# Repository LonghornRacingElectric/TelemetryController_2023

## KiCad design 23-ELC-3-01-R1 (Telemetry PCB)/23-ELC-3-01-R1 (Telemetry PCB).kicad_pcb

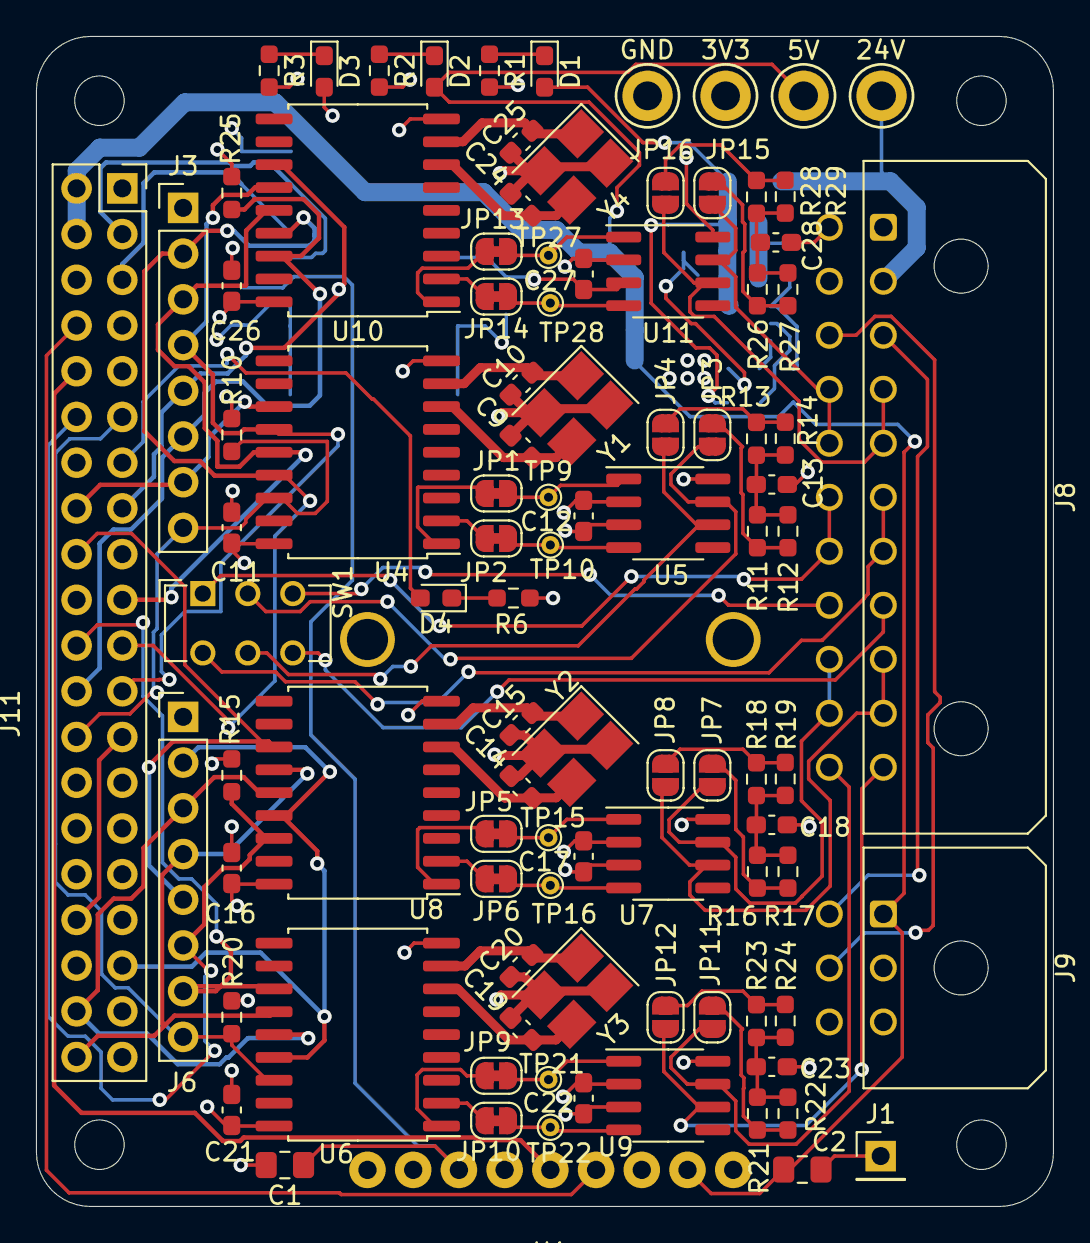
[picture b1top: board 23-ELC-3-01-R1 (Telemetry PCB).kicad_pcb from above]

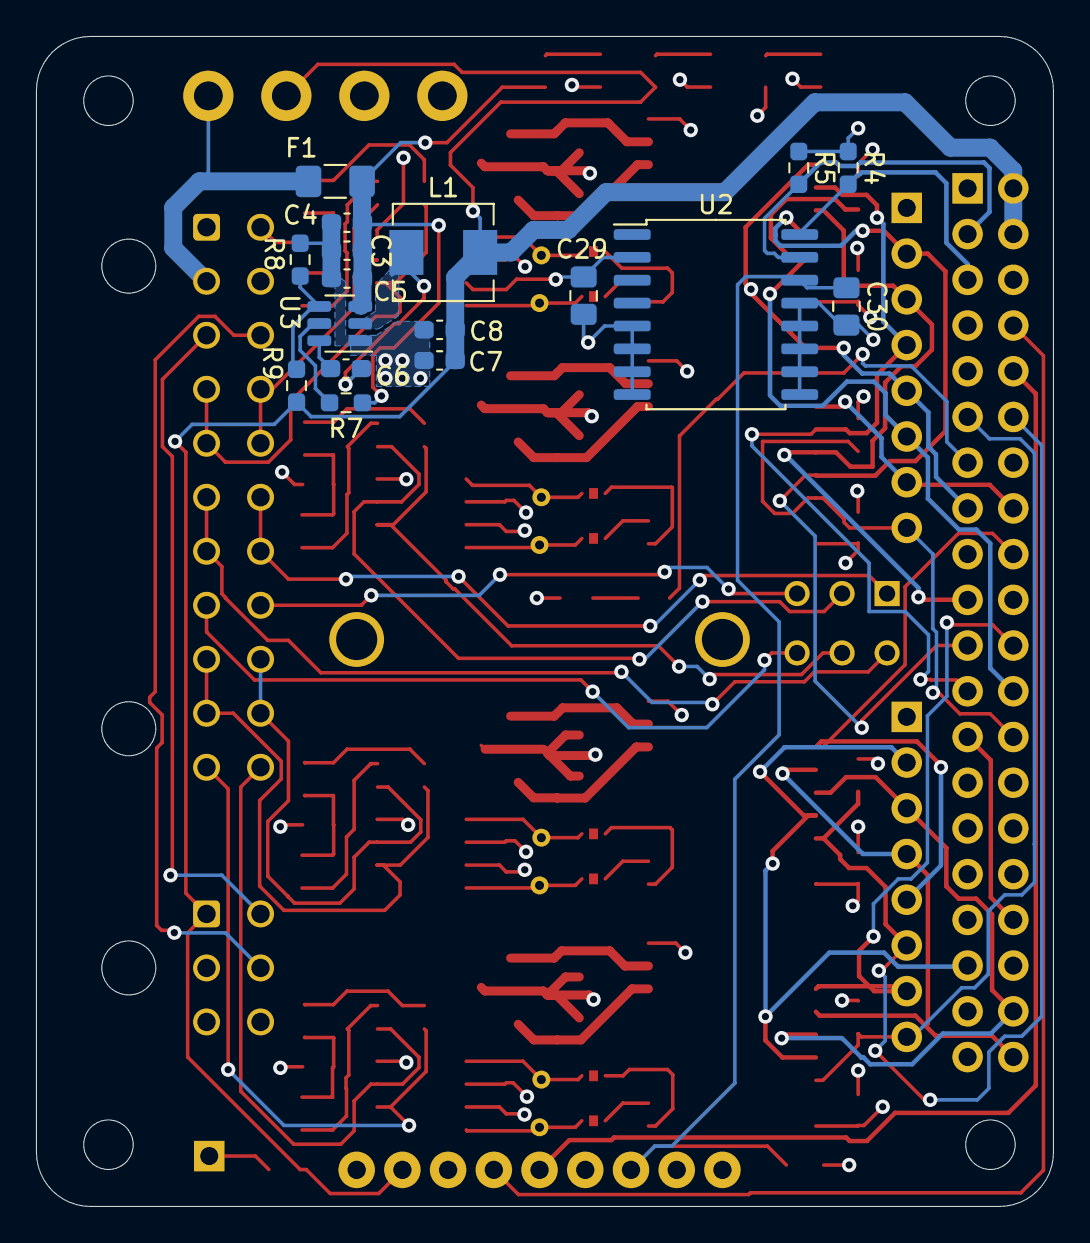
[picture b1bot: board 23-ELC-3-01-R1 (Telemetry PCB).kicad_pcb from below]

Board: 4 copper layers, 56.5 x 65.0 mm, 115 parts (17 on the bottom side), 83 nets.

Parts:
C1, C29, C30: 1uF; C_0805_2012Metric_Pad1.18x1.45mm_HandSolder
C2: 10uF; C_0805_2012Metric_Pad1.18x1.45mm_HandSolder
C3, C4: 10uF; C_0603_1608Metric_Pad1.08x0.95mm_HandSolder
C5, C6: 100nF; C_0603_1608Metric_Pad1.08x0.95mm_HandSolder
C7, C8: 22uF; C_0603_1608Metric_Pad1.08x0.95mm_HandSolder
C9, C10, C14, C15, C19, C20, C24, C25: 22pf; C_0603_1608Metric_Pad1.08x0.95mm_HandSolder
C11, C12, C16, C17, C21, C22, C26, C27: 0.1uf; C_0603_1608Metric_Pad1.08x0.95mm_HandSolder
C13, C18, C23, C28: 4.7nF; C_0603_1608Metric_Pad1.08x0.95mm_HandSolder
D1, D2, D3, D4: LED; LED_0603_1608Metric_Pad1.05x0.95mm_HandSolder
F1: 1A; Fuse_1206_3216Metric_Pad1.42x1.75mm_HandSolder
J1: Conn_01x01; PinHeader_1x01_P2.54mm_Vertical
J3, J6: Conn_01x08; PinHeader_1x08_P2.54mm_Vertical
J8: Conn_02x11_Top_Bottom; Molex_Micro-Fit_3.0_43045-2200_2x11_P3.00mm_Horizontal
J9: Conn_01x06; Molex_Micro-Fit_3.0_43045-0600_2x03_P3.00mm_Horizontal
J11: LHRE_Component_Library_Raspberry_Pi_4b; Raspberry_Pi_4B_Socketed_THT_FaceDown_MountingHoles
JP1, JP2, JP5, JP6, JP9, JP10, JP13, JP14: Jumper_2_Bridged; SolderJumper-2_P1.3mm_Bridged_RoundedPad1.0x1.5mm
JP3, JP4, JP7, JP8, JP11, JP12, JP15, JP16: NO_Jumper; SolderJumper-2_P1.3mm_Open_RoundedPad1.0x1.5mm
L1: 4u7; L_Sunlord_MWSA0518_5.4x5.2mm
R1: 3.3k; R_0603_1608Metric_Pad0.98x0.95mm_HandSolder
R2: 680; R_0603_1608Metric_Pad0.98x0.95mm_HandSolder
R3, R6: 470; R_0603_1608Metric_Pad0.98x0.95mm_HandSolder
R4, R5: 10k; R_0603_1608Metric_Pad0.98x0.95mm_HandSolder
R7, R8: 10K; R_0603_1608Metric_Pad0.98x0.95mm_HandSolder
R9: 54.9K; R_0603_1608Metric_Pad0.98x0.95mm_HandSolder
R10, R15, R20, R25: 100k; R_0603_1608Metric_Pad0.98x0.95mm_HandSolder
R11, R12, R13, R14, R16, R17, R18, R19, R21, R22, R23, R24, R26, R27, R28, R29: 120; R_0603_1608Metric_Pad0.98x0.95mm_HandSolder
SW1: SW_DPDT_x2; SW_CuK_JS202011CQN_DPDT_Straight
TP1, TP2, TP3, TP4: TestPoint; TestPoint_Keystone_5005-5009_Compact
TP9, TP10, TP15, TP16, TP21, TP22, TP27, TP28: TestPoint; TestPoint_THTPad_D1.0mm_Drill0.5mm
U1: LHRE_Component_Library_Adafruit_Ultimate_GPS_V3; Adafruit_Ultimate_GPS_V3
U2: DS3231M; SOIC-16W_7.5x10.3mm_P1.27mm
U3: LMR51420; SOT-23-6
U4, U6, U8, U10: MCP2515-xSO; SOIC-18W_7.5x11.6mm_P1.27mm
U5, U7, U9, U11: SN65HVD230; SOIC-8_3.9x4.9mm_P1.27mm
Y1, Y2, Y3, Y4: 16 MHz; Crystal_SMD_3225-4Pin_3.2x2.5mm_HandSoldering

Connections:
+3V3: C11.2, C12.2, C16.2, C17.2, C21.2, C22.2, C26.2, C27.2, C29.1, D3.2 (A), J11.1 (3V3), J11.17 (3V3), R4.1, R5.1, R10.1, R15.1, R20.1, R25.1, TP4.1, U2.2 (VCC), U4.18 (VDD), U5.3 (VCC), U6.18 (VDD), U7.3 (VCC), U8.18 (VDD), U9.3 (VCC), U10.18 (VDD), U11.3 (VCC)
+5V: C2.1, C7.1, C8.1, D2.2 (A), J9.1, J11.2 (5V), J11.4 (5V), L1.2, R9.2, TP3.1, U1.8 (VIN)
+24V: F1.2, J8.2, TP2.1
+BATT: C1.1, C30.1, U1.3 (VBAT), U2.14 (VBAT)
/3.3v_SCL: J11.5 (SCL/GPIO3), R4.2, U2.16 (SCL)
/3.3v_SDA: J11.3 (SDA/GPIO2), R5.2, U2.15 (SDA)
/Buck 24 to 5/EN: R7.2, U3.5 (EN)
/Buck 24 to 5/SW: C6.1, L1.1, U3.2 (SW)
/Buck 24 to 5/VBST: C6.2, U3.6 (VBST)
/Buck 24 to 5/VFB: R8.1, R9.1, U3.4 (VFB)
/Buck 24 to 5/V_in: C3.1, C4.1, C5.1, D1.2 (A), F1.1, R7.1, U3.3 (VIN)
/CAN0/CAN_RX: JP14.2 (B), U10.2 (RXCAN)
/CAN0/CAN_TX: JP13.1 (A), U10.1 (TXCAN)
/CAN1/CAN_RX: JP2.2 (B), U4.2 (RXCAN)
/CAN1/CAN_TX: JP1.1 (A), U4.1 (TXCAN)
/CAN2/CAN_RX: JP6.2 (B), U6.2 (RXCAN)
/CAN2/CAN_TX: JP5.1 (A), U6.1 (TXCAN)
/CAN3/CAN_RX: JP10.2 (B), U8.2 (RXCAN)
/CAN3/CAN_TX: JP9.1 (A), U8.1 (TXCAN)
/CAN_CS_0: J3.6, J11.24 (~CE0/GPIO8), R25.2, U10.16 (~CS)
/CAN_CS_1: J3.8, J11.26 (~CE1/GPIO7), R10.2, U4.16 (~CS)
/CAN_CS_2: J6.6, J11.12 (GPIO18/PWM0), R15.2, U6.16 (~CS)
/CAN_CS_3: J6.8, J11.11 (GPIO17), R20.2, U8.16 (~CS)
/CAN_H_0: J8.15, J8.16, JP15.1 (A), U11.7 (CANH)
/CAN_H_1: JP3.1 (A), SW1.2 (B), U5.7 (CANH)
/CAN_H_1_A: J8.17, J8.18, SW1.1 (A)
/CAN_H_1_B: J8.19, SW1.3 (C)
/CAN_H_2: J8.20, J8.21, JP7.1 (A), U7.7 (CANH)
/CAN_H_3: J8.22, JP11.1 (A), U9.7 (CANH)
/CAN_INT_0: J3.5, J11.15 (GPIO22), U10.12 (~INT)
/CAN_INT_1: J3.7, J11.16 (GPIO23), U4.12 (~INT)
/CAN_INT_2: J6.5, J11.18 (GPIO24), U6.12 (~INT)
/CAN_INT_3: J6.7, J11.22 (GPIO25), U8.12 (~INT)
/CAN_L_0: J8.4, J8.5, JP16.1 (A), U11.6 (CANL)
/CAN_L_1: JP4.1 (A), SW1.5 (B), U5.6 (CANL)
/CAN_L_1_A: J8.6, J8.7, SW1.4 (A)
/CAN_L_1_B: J8.8, SW1.6 (C)
/CAN_L_2: J8.9, J8.10, JP8.1 (A), U7.6 (CANL)
/CAN_L_3: J8.11, JP12.1 (A), U9.6 (CANL)
/CAN_MISO_01: J3.2, J11.21 (MISO0/GPIO9), U4.15 (SO), U10.15 (SO)
/CAN_MISO_23: J6.2, J11.35 (GPIO19/MISO1), U6.15 (SO), U8.15 (SO)
/CAN_MOSI_01: J3.3, J11.19 (MOSI0/GPIO10), U4.14 (SI), U10.14 (SI)
/CAN_MOSI_23: J6.3, J11.38 (GPIO20/MOSI1), U6.14 (SI), U8.14 (SI)
/CAN_SCK_01: J3.4, J11.23 (SCLK0/GPIO11), U4.13 (SCK), U10.13 (SCK)
/CAN_SCK_23: J6.4, J11.40 (GPIO21/SCLK1), U6.13 (SCK), U8.13 (SCK)
/GPS_RX: J11.8 (GPIO14/TXD), U1.6 (RX)
/GPS_TX: J11.10 (GPIO15/RXD), U1.5 (TX)
/TSAL_G: J8.3, J9.4
/TSAL_R: J8.14, J9.5
GND: C1.2, C2.2, C3.2, C4.2, C5.2, C7.2, C8.2, C9.1, C10.2, C11.1, C12.1, C13.2, C14.1, C15.2, C16.1, C17.1, C18.2, C19.1, C20.2, C21.1, C22.1, C23.2, C24.1, C25.2, C26.1, C27.1, C28.2, C29.2, C30.2, J1.1, J3.1, J6.1, J8.1, J8.12, J9.2, J9.3, J11.6 (GND), J11.9 (GND), J11.14 (GND), J11.20 (GND), J11.25 (GND), J11.30 (GND), J11.34 (GND), J11.39 (GND), R1.2, R2.2, R3.2, R6.2, R8.2, TP1.1, U1.7 (GND), U2.5 (GND), U2.6 (GND), U2.7 (GND), U2.8 (GND), U2.9 (GND), U2.10 (GND), U2.11 (GND), U2.12 (GND), U2.13 (GND), U3.1 (GND), U4.9 (VSS), U5.2 (GND), U5.8 (Rs), U6.9 (VSS), U7.2 (GND), U7.8 (Rs), U8.9 (VSS), U9.2 (GND), U9.8 (Rs), U10.9 (VSS), U11.2 (GND), U11.8 (Rs), Y1.2, Y1.4, Y2.2, Y2.4, Y3.2, Y3.4, Y4.2, Y4.4
unnamed: C9.2, U4.7 (OSC2), Y1.3
unnamed: C10.1, U4.8 (OSC1), Y1.1
unnamed: C13.1, R11.2, R12.2, R13.2, R14.2
unnamed: C14.2, U6.7 (OSC2), Y2.3
unnamed: C15.1, U6.8 (OSC1), Y2.1
unnamed: C18.1, R16.2, R17.2, R18.2, R19.2
unnamed: C19.2, U8.7 (OSC2), Y3.3
unnamed: C20.1, U8.8 (OSC1), Y3.1
unnamed: C23.1, R21.2, R22.2, R23.2, R24.2
unnamed: C24.2, U10.7 (OSC2), Y4.3
unnamed: C25.1, U10.8 (OSC1), Y4.1
unnamed: C28.1, R26.2, R27.2, R28.2, R29.2
unnamed: D1.1 (K), R1.1
unnamed: D2.1 (K), R2.1
unnamed: D3.1 (K), R3.1
unnamed: D4.1 (K), R6.1
unnamed: D4.2 (A), J11.13 (GPIO27)
unnamed: JP1.2 (B), TP9.1, U5.1 (D)
unnamed: JP2.1 (A), TP10.1, U5.4 (R)
unnamed: JP3.2 (B), R11.1, R12.1
unnamed: JP4.2 (B), R13.1, R14.1
unnamed: JP5.2 (B), TP15.1, U7.1 (D)
unnamed: JP6.1 (A), TP16.1, U7.4 (R)
unnamed: JP7.2 (B), R16.1, R17.1
unnamed: JP8.2 (B), R18.1, R19.1
unnamed: JP9.2 (B), TP21.1, U9.1 (D)
unnamed: JP10.1 (A), TP22.1, U9.4 (R)
unnamed: JP11.2 (B), R21.1, R22.1
unnamed: JP12.2 (B), R23.1, R24.1
unnamed: JP13.2 (B), TP27.1, U11.1 (D)
unnamed: JP14.1 (A), TP28.1, U11.4 (R)
unnamed: JP15.2 (B), R26.1, R27.1
unnamed: JP16.2 (B), R28.1, R29.1

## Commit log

2022-09-26 Added 2023KicadLibrary
2022-10-09 Added telemetry PCB and made a couple of changes
2022-10-09 Fixed file names for 2023
2022-10-30 Added some CAN hardware
2022-11-07 Finished CAN circuits probably
2022-11-27 Ready for review
2022-12-17 Schematic finished, working on layout
2022-12-19 First draft of layout
2023-01-08 Fixed review notes and made 4 layer
2023-01-09 Changes for reference legibility, trace clearance, and through hole solder mask
2023-01-09 Updated kicad library reference
